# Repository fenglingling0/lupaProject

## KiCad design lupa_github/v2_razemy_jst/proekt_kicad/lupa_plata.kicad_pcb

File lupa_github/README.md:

# lupa_plata

Handheld camera magnifier. ESP32-S3-WROOM-1-N16R8, OV5640 (DVP, 24-pin FPC), 4-layer, 28.2 x 67.1 mm, KiCad 9. Two-sided SMT assembly at JLCPCB.

## Architecture

- Power: USB-C -> BQ21061 (charger / power path) -> TPS63802 buck-boost -> 3V3. Hard on/off via SPDT on the TPS63802 EN. Camera rails: ME6211 (2V8), TLV75515 (1V5).
- Audio: PDM mic (MSM261) direct to GPIO, MAX98357A I2S amp. Storage: microSD over SPI. IMU: QMI8658B (INT on an RTC GPIO, wake-up).
- Battery sense: 100k/100k divider gated by TMUX1101 (IO18 enable, IO16 sense).
- Programming and logging over native USB (IO19/IO20); UART0 pins are used for I2S.
- Pin map: `pin_list.csv` / `pin_list_en.csv`.

## Stackup / layout

F.Cu / GND / 3V3 plane + slow signals / B.Cu. Vias 0.3/0.15 (JLCPCB 0.15 mm via option required), in-pad vias on the BQ21061 DSBGA (epoxy-filled, capped). Bottom side: low-profile parts only (passives up to 1206, SOT-23-5, SC70-5).

## Versions

| | v1_ploschadki_pod_payku | v2_razemy_jst |
|---|---|---|
| Battery / speaker / trigger | solder pads | JST PH 2-pin, vertical THT (B2B-PH-K-S) |
| Battery NTC | pads (J6) | removed, TS biased by R3 10k |
| Mic | MSM261D3526H1CPM (no JLCPCB stock) | MSM261DDB019 (C51928210) |
| DRC / ERC | clean | clean |

v2 is current. Differences beyond the table: D1/R24 and a few passives moved; CAM_VSYNC routed on the inner layer along the right edge.

## Status

Not built yet. DRC (with schematic parity) and ERC are clean; BOM has an LCSC number for every part.

Not verified on hardware:
- Start-up and charging with USB only (no battery).
- Placement rotation of polarized parts in the JLCPCB viewer (U1, U2, U3, X1, J2, J4, MK1).
- IO16 is ADC2: unusable while Wi-Fi is active.
- JST PH pin 1 = BAT+; battery pack polarity varies by vendor.

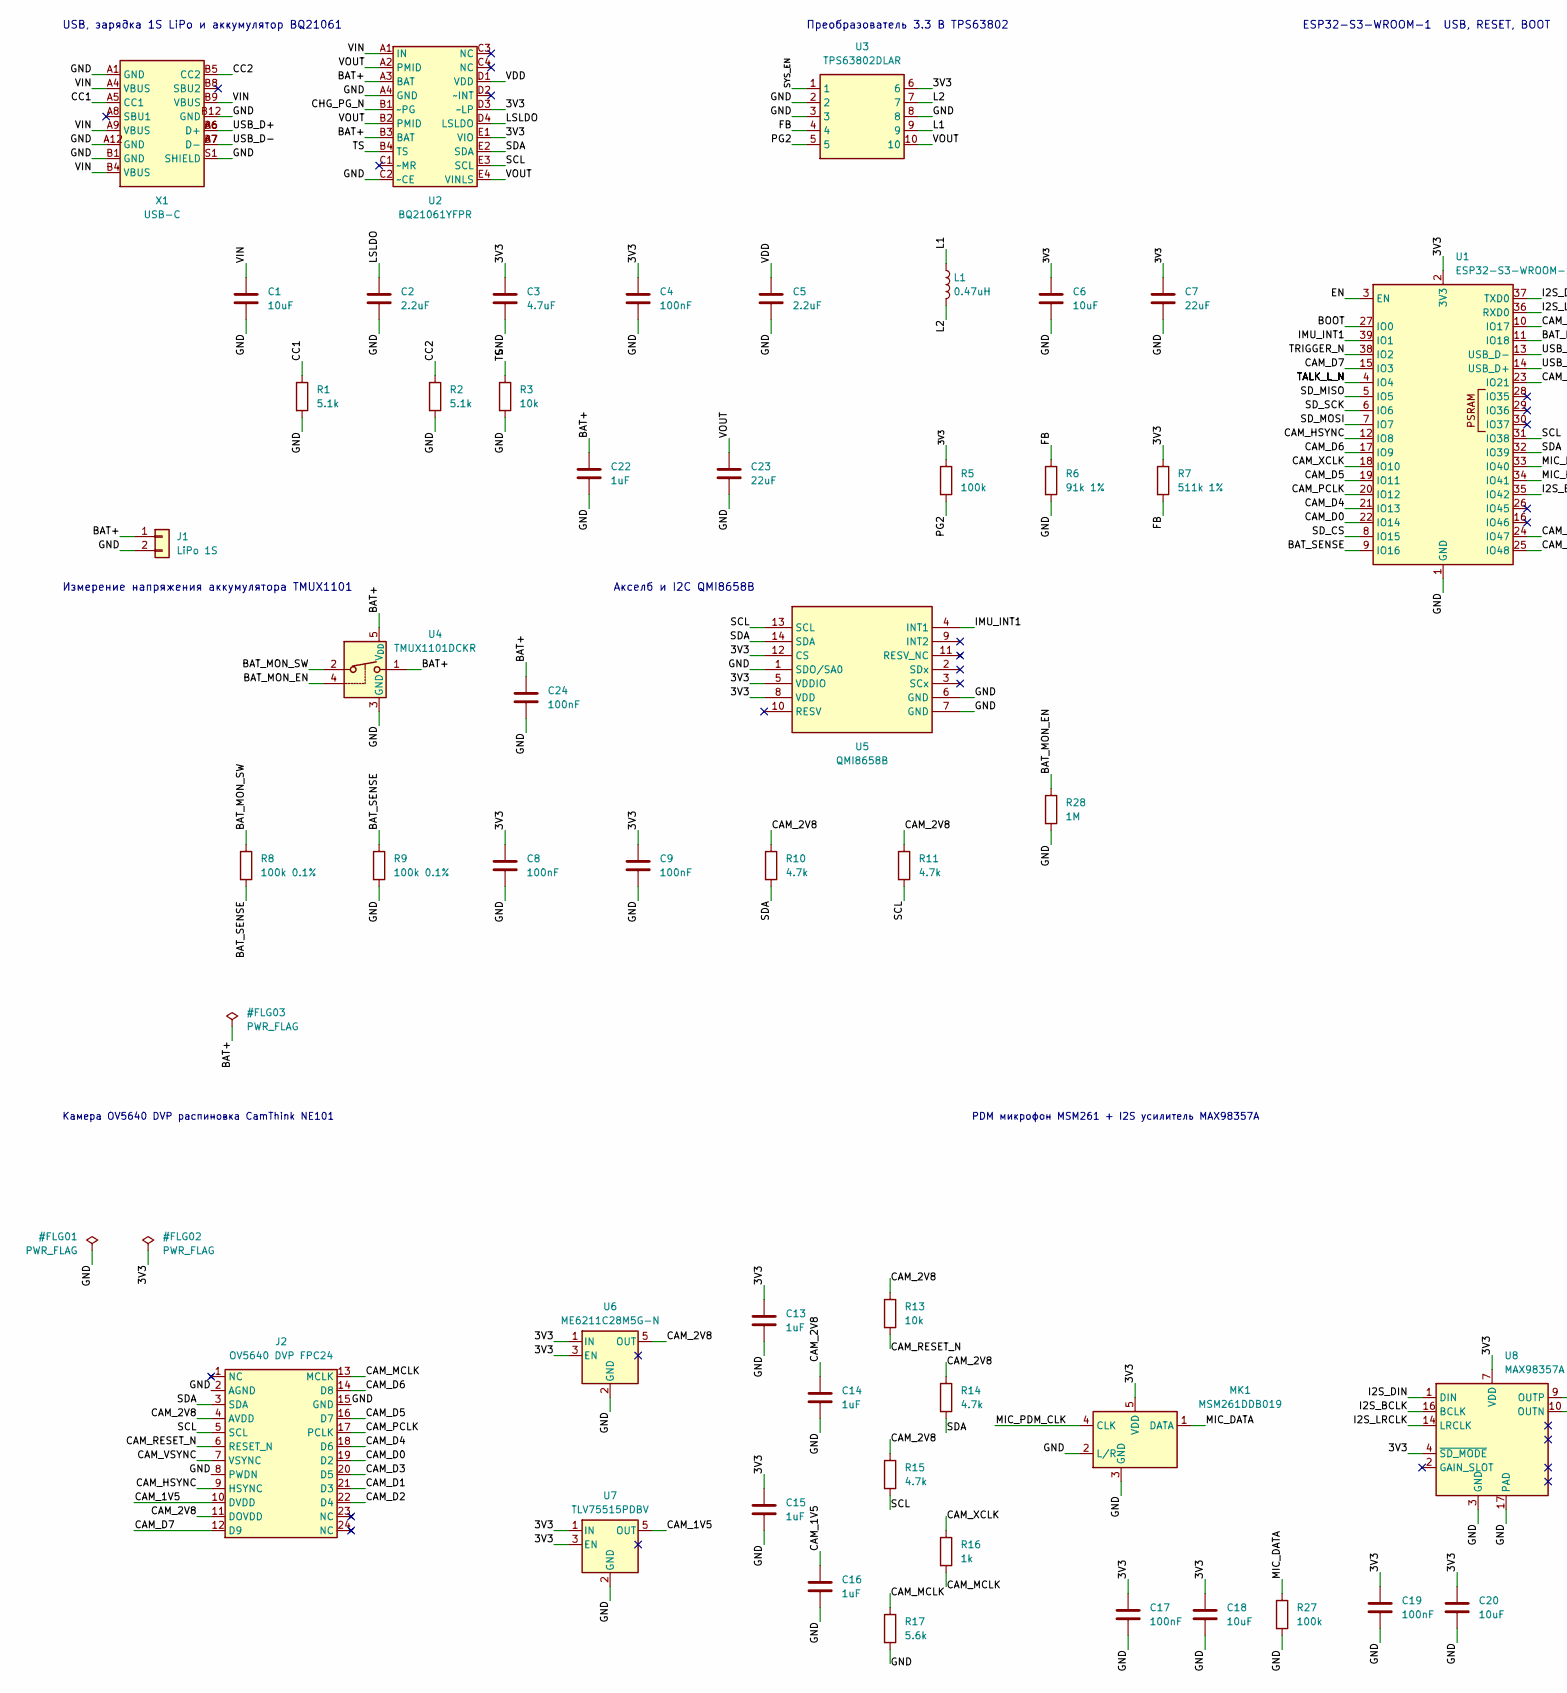
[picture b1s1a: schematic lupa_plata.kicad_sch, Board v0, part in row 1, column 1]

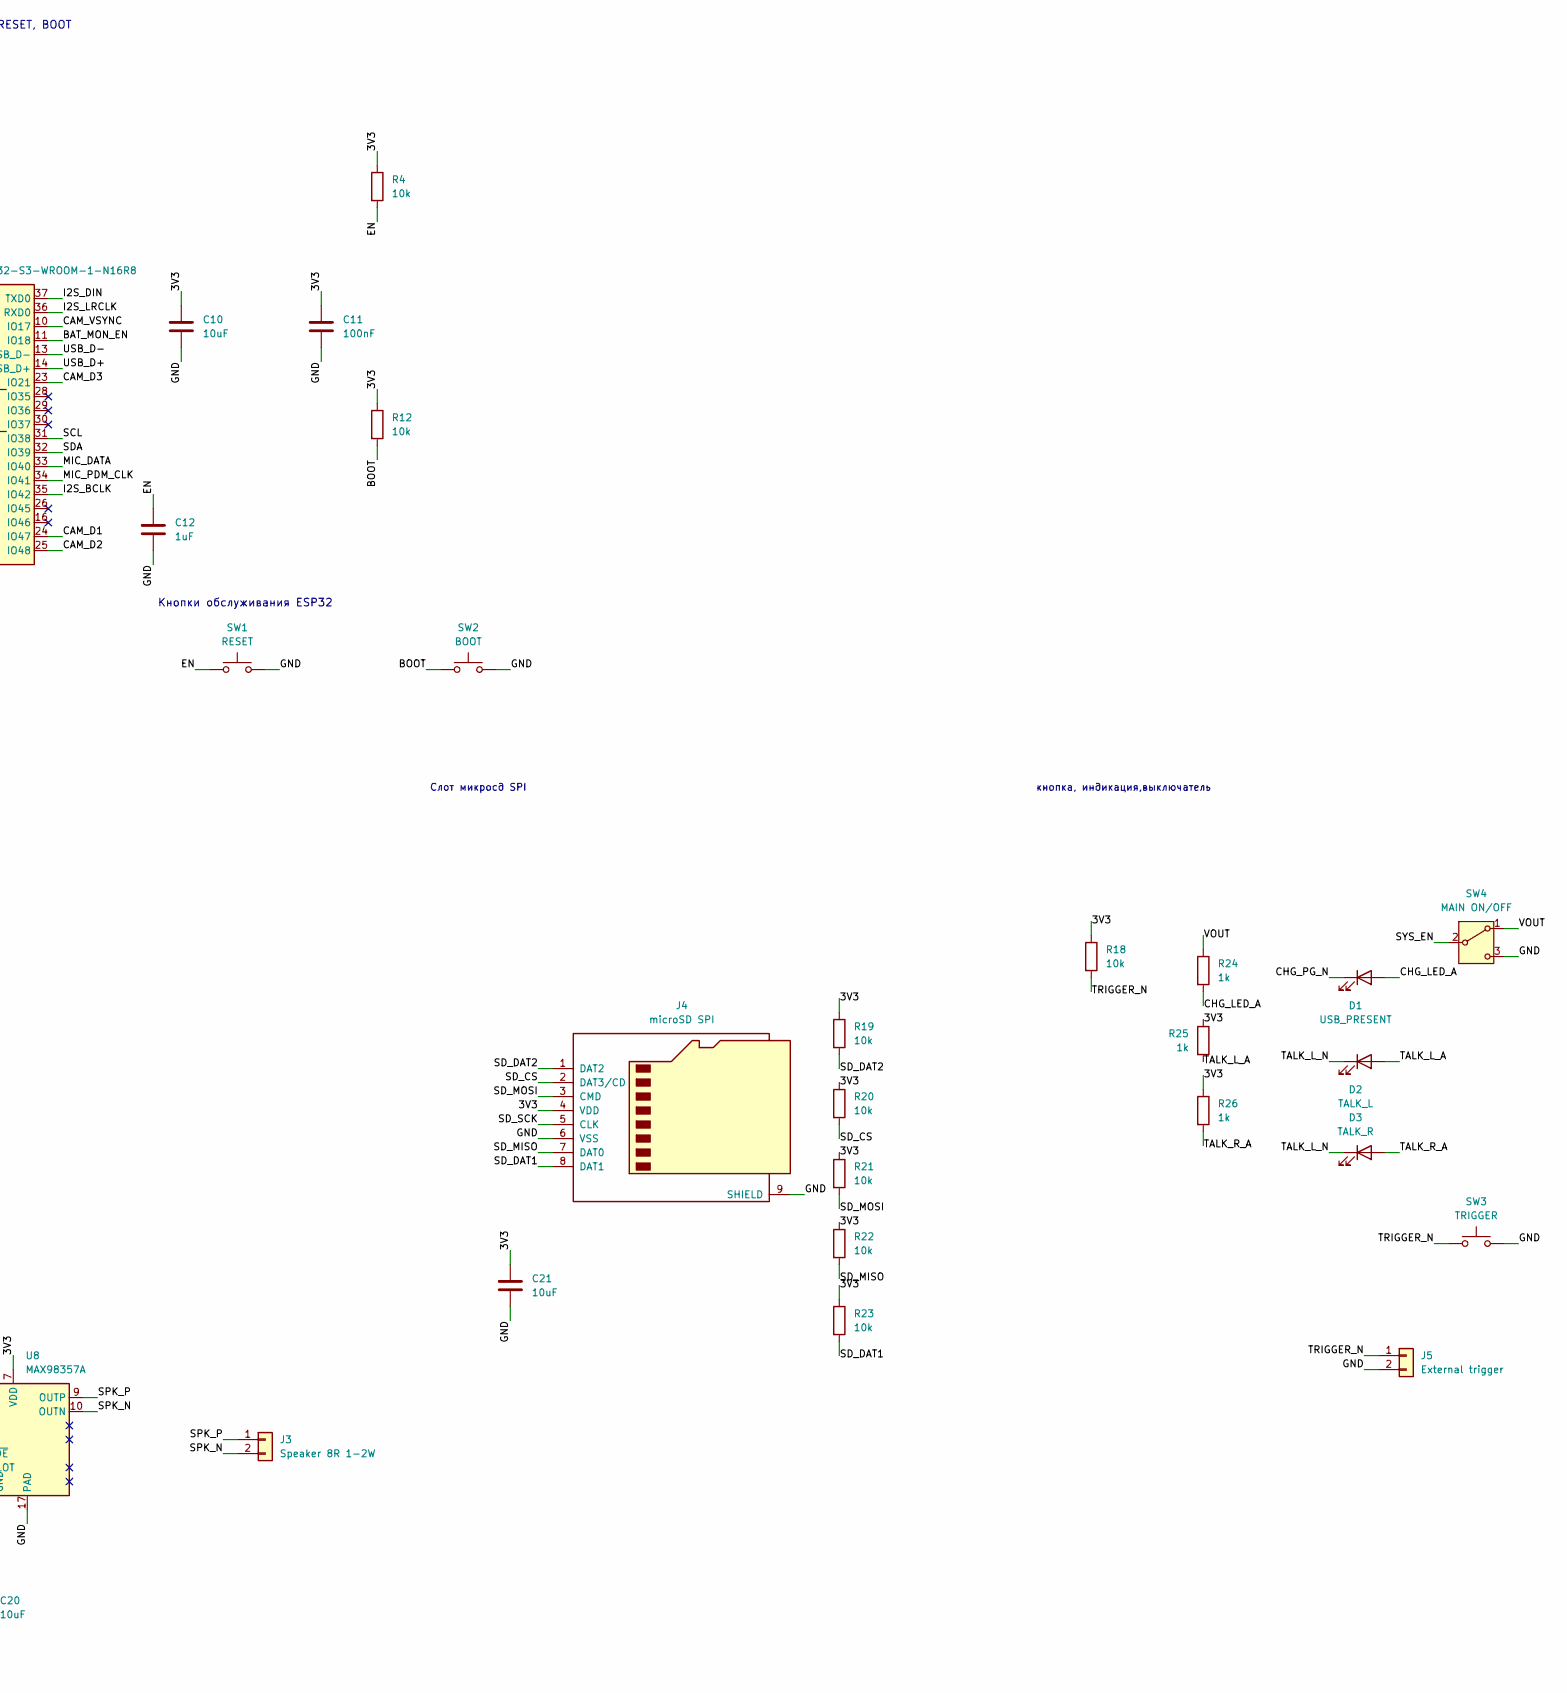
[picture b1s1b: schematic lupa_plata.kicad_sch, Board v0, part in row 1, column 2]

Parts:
C1, C6: 10uF; C_0402_1005Metric
C2, C5: 2.2uF; C_0402_1005Metric
C3: 4.7uF; C_0402_1005Metric
C4, C24: 100nF; C_0402_1005Metric
C7: 22uF; C_1206_3216Metric
C8, C9, C11, C17, C19: 100nF; C_0603_1608Metric
C10, C18, C20, C21: 10uF; C_0805_2012Metric
C12, C13, C14, C15, C16: 1uF; C_0603_1608Metric
C22: 1uF; C_0402_1005Metric
C23: 22uF; C_0603_1608Metric
D1: USB_PRESENT; LED_0603_1608Metric
D2: TALK_L; LED_0603_1608Metric
D3: TALK_R; LED_0603_1608Metric
J1: LiPo 1S; JST_PH_B2B-PH-K_1x02_P2.00mm_Vertical
J2: OV5640 DVP FPC24; Hirose_FH12-24S-0.5SH_1x24-1MP_P0.50mm_Horizontal
J3: Speaker 8R 1-2W; JST_PH_B2B-PH-K_1x02_P2.00mm_Vertical
J4: microSD SPI; microSD_HC_Wuerth_693072010801
J5: External trigger; JST_PH_B2B-PH-K_1x02_P2.00mm_Vertical
L1: 0.47uH; L_Changjiang_FTC201610S; MPN TFM201610GHM-R47MTAA
MK1: MSM261DDB019; MPN MSM261DDB019
R1, R2: 5.1k; R_0603_1608Metric
R3: 10k; R_0402_1005Metric
R4, R12, R13, R18, R19, R20, R21, R22, R23: 10k; R_0603_1608Metric
R5: 100k; R_0402_1005Metric
R6: 91k 1%; R_0402_1005Metric
R7: 511k 1%; R_0402_1005Metric
R8, R9: 100k 0.1%; R_0603_1608Metric
R10, R11, R14, R15: 4.7k; R_0603_1608Metric
R16, R24, R25, R26: 1k; R_0603_1608Metric
R17: 5.6k; R_0603_1608Metric
R27: 100k; R_0603_1608Metric
R28: 1M; R_0603_1608Metric
SW1: RESET; SW_SPST_B3U-1000P
SW2: BOOT; SW_SPST_B3U-1000P
SW3: TRIGGER; SW_SPST_B3U-1000P
SW4: MAIN ON/OFF; SW_SPDT_PCM12; MPN JS102011SAQN
U1: ESP32-S3-WROOM-1-N16R8; ESP32-S3-WROOM-1
U2: BQ21061YFPR; Texas_YFP0020_DSBGA-20_tight
U3: TPS63802DLAR; TPS63802_VSON-HR-10_2x3mm
U4: TMUX1101DCKR; SOT-353_SC-70-5
U5: QMI8658B; LGA-14_3x2.5mm_P0.5mm_LayoutBorder3x4y
U6: ME6211C28M5G-N; SOT-23-5
U7: TLV75515PDBV; SOT-23-5
U8: MAX98357A; TQFN-16-1EP_3x3mm_P0.5mm_EP1.23x1.23mm
X1: USB-C; USB_C_Receptacle_GCT_USB4110

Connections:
/3V3: C3.1, C4.1, C6.1, C7.1, C8.1, C9.1, C10.1, C11.1, C13.1, C15.1, C17.1, C18.1, C19.1, C20.1, C21.1, J4.4 (VDD), MK1.5 (VDD), R4.1, R5.1, R7.1, R12.1, R18.1, R19.1, R20.1, R21.1, R22.1, R23.1, R25.1, R26.1, U1.2 (3V3), U2.D3 (~LP), U2.E1 (VIO), U3.6, U5.5 (VDDIO), U5.8 (VDD), U5.12 (CS), U6.1 (IN), U6.3 (EN), U7.1 (IN), U7.3 (EN), U8.4 (~SD_MODE), U8.7 (VDD), U8.8 (VDD)
/BAT+: C22.1, C24.1, J1.1, U2.A3 (BAT), U2.B3 (BAT), U4.1, U4.5 (V_{DD})
/BAT_MON_EN: R28.1, U1.11 (IO18), U4.4
/BAT_MON_SW: R8.1, U4.2
/BAT_SENSE: R8.2, R9.1, U1.9 (IO16)
/BOOT: R12.2, SW2.1, U1.27 (IO0)
/CAM_1V5: C16.1, J2.10 (DVDD), U7.5 (OUT)
/CAM_2V8: C14.1, J2.4 (AVDD), J2.11 (DOVDD), R10.1, R11.1, R13.1, R14.1, R15.1, U6.5 (OUT)
/CAM_D0: J2.19 (D2), U1.22 (IO14)
/CAM_D1: J2.21 (D3), U1.24 (IO47)
/CAM_D2: J2.22 (D4), U1.25 (IO48)
/CAM_D3: J2.20 (D5), U1.23 (IO21)
/CAM_D4: J2.18 (D6), U1.21 (IO13)
/CAM_D5: J2.16 (D7), U1.19 (IO11)
/CAM_D6: J2.14 (D8), U1.17 (IO9)
/CAM_D7: J2.12 (D9), U1.15 (IO3)
/CAM_HSYNC: J2.9 (HSYNC), U1.12 (IO8)
/CAM_MCLK: J2.13 (MCLK), R16.2, R17.1
/CAM_PCLK: J2.17 (PCLK), U1.20 (IO12)
/CAM_RESET_N: J2.6 (RESET_N), R13.2
/CAM_VSYNC: J2.7 (VSYNC), U1.10 (IO17)
/CAM_XCLK: R16.1, U1.18 (IO10)
/CC1: R1.1, X1.A5 (CC1)
/CC2: R2.1, X1.B5 (CC2)
/CHG_LED_A: D1.2 (A), R24.2
/CHG_PG_N: D1.1 (K), U2.B1 (~PG)
/EN: C12.1, R4.2, SW1.1, U1.3 (EN)
/FB: R6.1, R7.2, U3.4
/GND: C1.2, C2.2, C3.2, C4.2, C5.2, C6.2, C7.2, C8.2, C9.2, C10.2, C11.2, C12.2, C13.2, C14.2, C15.2, C16.2, C17.2, C18.2, C19.2, C20.2, C21.2, C22.2, C23.2, C24.2, J1.2, J2.2 (AGND), J2.8 (PWDN), J2.15 (GND), J4.6 (VSS), J4.9 (SHIELD), J5.2, MK1.2 (L/R), MK1.3 (GND), R1.2, R2.2, R3.2, R6.2, R9.2, R17.2, R27.2, R28.2, SW1.2, SW2.2, SW3.2, SW4.3 (C), U1.1 (GND), U1.40 (GND), U1.41 (GND), U2.A4 (GND), U2.C2 (~CE), U3.2, U3.3, U3.8, U4.3 (GND), U5.1 (SDO/SA0), U5.6 (GND), U5.7 (GND), U6.2 (GND), U7.2 (GND), U8.3 (GND), U8.11 (GND), U8.15 (GND), U8.17 (PAD), X1.A1 (GND), X1.A12 (GND), X1.B1 (GND), X1.B12 (GND), X1.S1 (SHIELD)
/I2S_BCLK: U1.35 (IO42), U8.16 (BCLK)
/I2S_DIN: U1.37 (TXD0), U8.1 (DIN)
/I2S_LRCLK: U1.36 (RXD0), U8.14 (LRCLK)
/IMU_INT1: U1.39 (IO1), U5.4 (INT1)
/L1: L1.1, U3.9
/L2: L1.2, U3.7
/LSLDO: C2.1, U2.D4 (LSLDO)
/MIC_DATA: MK1.1 (DATA), R27.1, U1.33 (IO40)
/MIC_PDM_CLK: MK1.4 (CLK), U1.34 (IO41)
/PG2: R5.2, U3.5
/SCL: J2.5 (SCL), R11.2, R15.2, U1.31 (IO38), U2.E3 (SCL), U5.13 (SCL)
/SDA: J2.3 (SDA), R10.2, R14.2, U1.32 (IO39), U2.E2 (SDA), U5.14 (SDA)
/SD_CS: J4.2 (DAT3/CD), R20.2, U1.8 (IO15)
/SD_DAT1: J4.8 (DAT1), R23.2
/SD_DAT2: J4.1 (DAT2), R19.2
/SD_MISO: J4.7 (DAT0), R22.2, U1.5 (IO5)
/SD_MOSI: J4.3 (CMD), R21.2, U1.7 (IO7)
/SD_SCK: J4.5 (CLK), U1.6 (IO6)
/SPK_N: J3.2, U8.10 (OUTN)
/SPK_P: J3.1, U8.9 (OUTP)
/SYS_EN: SW4.2 (B), U3.1
/TALK_L_A: D2.2 (A), R25.2
/TALK_L_N: D2.1 (K), D3.1 (K), U1.4 (IO4)
/TALK_R_A: D3.2 (A), R26.2
/TRIGGER_N: J5.1, R18.2, SW3.1, U1.38 (IO2)
/TS: R3.1, U2.B4 (TS)
/USB_D+: U1.14 (USB_D+), X1.A6 (D+), X1.B6 (D+)
/USB_D-: U1.13 (USB_D-), X1.A7 (D-), X1.B7 (D-)
/VDD: C5.1, U2.D1 (VDD)
/VIN: C1.1, U2.A1 (IN), X1.A4 (VBUS), X1.A9 (VBUS), X1.B4 (VBUS), X1.B9 (VBUS)
/VOUT: C23.1, R24.1, SW4.1 (A), U2.A2 (PMID), U2.B2 (PMID), U2.E4 (VINLS), U3.10

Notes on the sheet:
Преобразователь 3.3 В TPS63802
Слот микросд SPI
USB, зарядка 1S LiPo и аккумулятор BQ21061
Камера OV5640 DVP распиновка CamThink NE101
Кнопки обслуживания ESP32
PDM микрофон MSM261 + I2S усилитель MAX98357A
Измерение напряжения аккумулятора TMUX1101
ESP32-S3-WROOM-1 USB, RESET, BOOT
Акселб и I2C QMI8658B
кнопка, индикация,выключатель

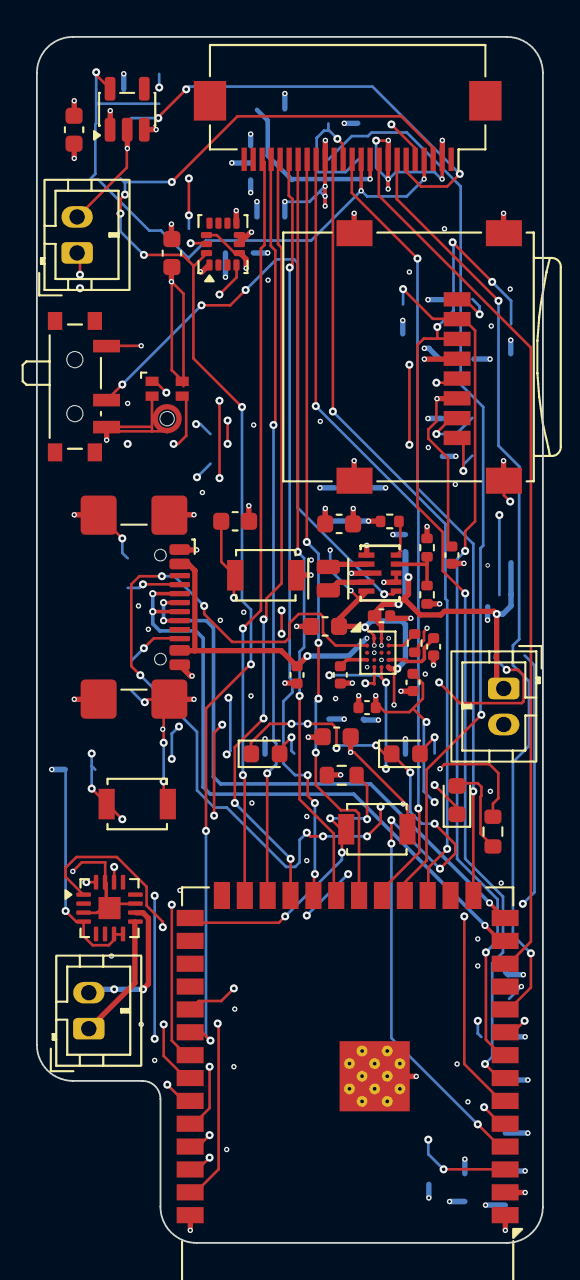
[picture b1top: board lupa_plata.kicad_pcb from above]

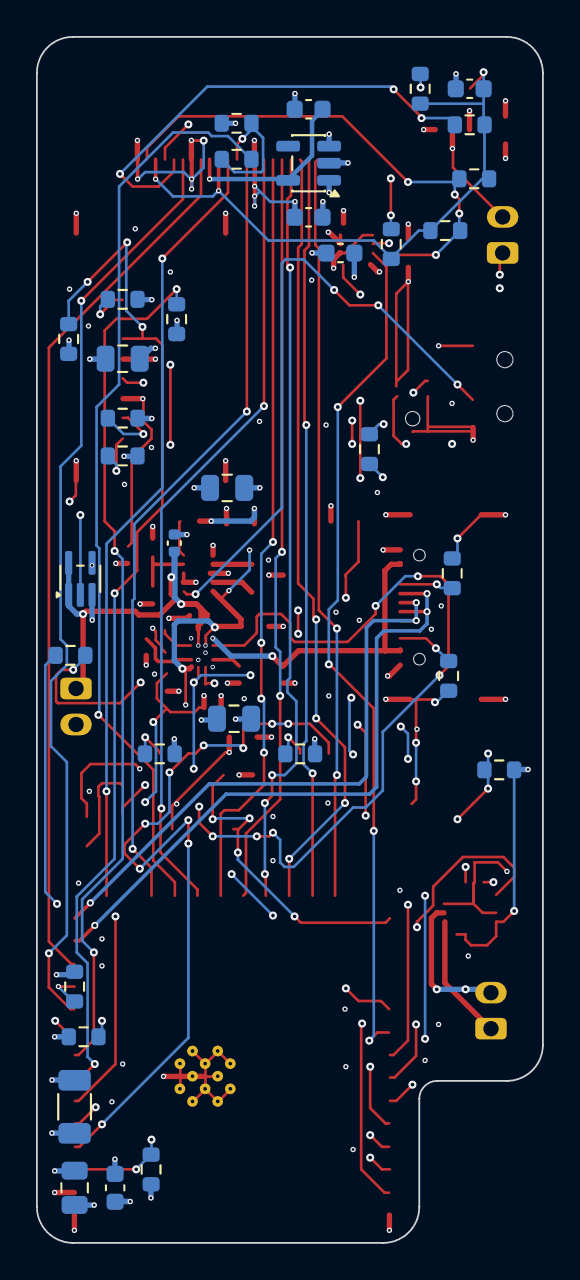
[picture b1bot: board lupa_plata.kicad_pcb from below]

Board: 4 copper layers, 28.1 x 67.0 mm, 75 parts (35 on the bottom side), 60 nets.

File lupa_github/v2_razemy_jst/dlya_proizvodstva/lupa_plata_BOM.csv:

"Comment","Designator","Footprint","LCSC Part #"
"10uF","C1,C6","C_0402_1005Metric","C315248"
"2.2uF","C2,C5","C_0402_1005Metric","C107370"
"4.7uF","C3","C_0402_1005Metric","C23733"
"100nF","C4,C24","C_0402_1005Metric","C1525"
"22uF","C7","C_1206_3216Metric","C12891"
"100nF","C8,C9,C11,C17,C19","C_0603_1608Metric","C14663"
"10uF","C10,C18,C20,C21","C_0805_2012Metric","C15850"
"1uF","C12,C13,C14,C15,C16","C_0603_1608Metric","C15849"
"1uF","C22","C_0402_1005Metric","C52923"
"22uF","C23","C_0603_1608Metric","C59461"
"USB_PRESENT","D1","LED_0603_1608Metric","C2286"
"TALK_L","D2","LED_0603_1608Metric","C2286"
"TALK_R","D3","LED_0603_1608Metric","C2286"
"LiPo 1S","J1","JST_PH_B2B-PH-K_1x02_P2.00mm_Vertical","C131337"
"OV5640 DVP FPC24","J2","Hirose_FH12-24S-0.5SH_1x24-1MP_P0.50mm_Horizontal","C202112"
"Speaker 8R 1-2W","J3","JST_PH_B2B-PH-K_1x02_P2.00mm_Vertical","C131337"
"microSD SPI","J4","microSD_HC_Wuerth_693072010801","C5912397"
"External trigger","J5","JST_PH_B2B-PH-K_1x02_P2.00mm_Vertical","C131337"
"0.47uH","L1","L_Changjiang_FTC201610S","C89446"
"MSM261DDB019","MK1","MSM261DDB019","C51928210"
"5.1k","R1,R2","R_0603_1608Metric","C23186"
"10k","R3","R_0402_1005Metric","C25744"
"10k","R4,R12,R13,R18,R19,R20,R21,R22,R23","R_0603_1608Metric","C25804"
"100k","R5","R_0402_1005Metric","C25741"
"91k 1%","R6","R_0402_1005Metric","C4147"
"511k 1%","R7","R_0402_1005Metric","C64042"
"100k 0.1%","R8,R9","R_0603_1608Metric","C335088"
"4.7k","R10,R11,R14,R15","R_0603_1608Metric","C23162"
"1k","R16,R24,R25,R26","R_0603_1608Metric","C21190"
"5.6k","R17","R_0603_1608Metric","C23189"
"100k","R27","R_0603_1608Metric","C25803"
"1M","R28","R_0603_1608Metric","C22935"
"RESET","SW1","SW_SPST_B3U-1000P","C231329"
"BOOT","SW2","SW_SPST_B3U-1000P","C231329"
"TRIGGER","SW3","SW_SPST_B3U-1000P","C231329"
"MAIN ON/OFF","SW4","SW_SPDT_PCM12","C221660"
"ESP32-S3-WROOM-1-N16R8","U1","ESP32-S3-WROOM-1","C2913202"
"BQ21061YFPR","U2","Texas_YFP0020_DSBGA-20_tight","C2869893"
"TPS63802DLAR","U3","TPS63802_VSON-HR-10_2x3mm","C2845237"
"TMUX1101DCKR","U4","SOT-353_SC-70-5","C2673506"
"QMI8658B","U5","LGA-14_3x2.5mm_P0.5mm_LayoutBorder3x4y","C5380158"
"ME6211C28M5G-N","U6","SOT-23-5","C53099"
"TLV75515PDBV","U7","SOT-23-5","C2867152"
"MAX98357A","U8","TQFN-16-1EP_3x3mm_P0.5mm_EP1.23x1.23mm","C910544"
"USB-C","X1","USB_C_Receptacle_GCT_USB4110","C5143397"
